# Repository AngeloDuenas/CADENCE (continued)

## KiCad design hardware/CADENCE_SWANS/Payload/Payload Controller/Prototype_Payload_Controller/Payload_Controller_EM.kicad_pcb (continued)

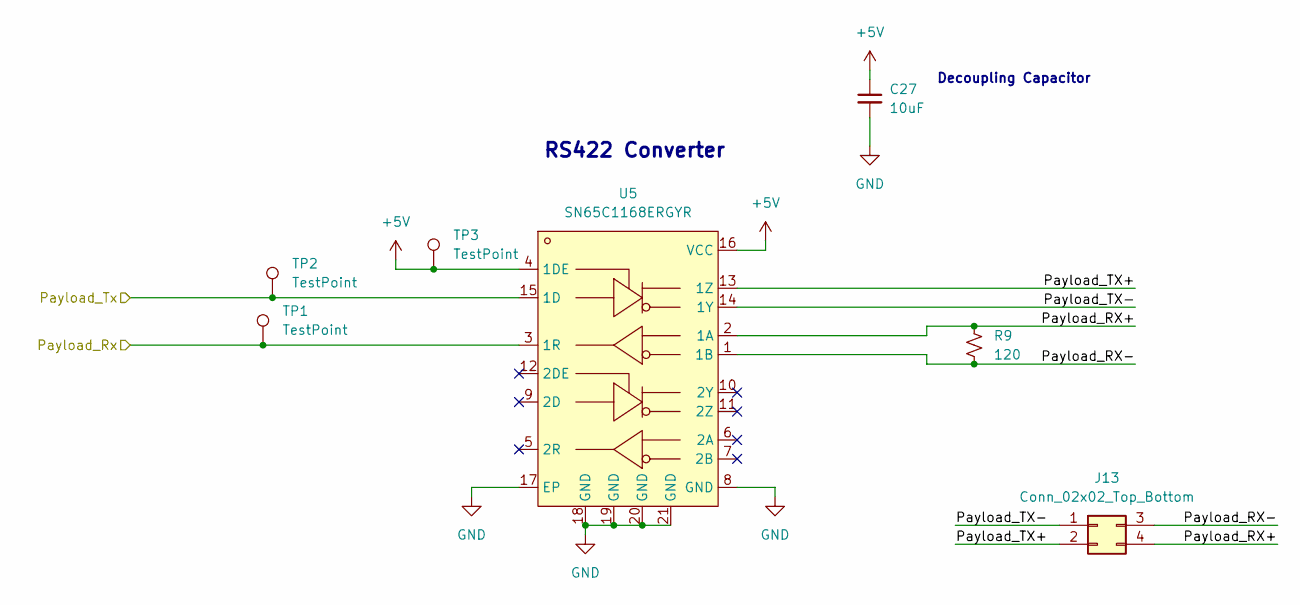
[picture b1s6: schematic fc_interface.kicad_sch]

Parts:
C27: 10uF; C_0603_1608Metric
J13: Conn_02x02_Top_Bottom; Hirose_DF11-4DP-2DSA_2x02_P2.00mm_Vertical
R9: 120; R_0603_1608Metric
TP1, TP2, TP3: TestPoint; TestPoint_Pad_1.0x1.0mm
U5: SN65C1168ERGYR; LCSC Part C201679

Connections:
+5V: C27.1, TP3.1, U5.4 (1DE), U5.16 (VCC); also elsewhere on the board
/Flight Computer Interface/Payload_RX+: J13.4, R9.1, U5.2 (1A)
/Flight Computer Interface/Payload_RX-: J13.3, R9.2, U5.1 (1B)
/Flight Computer Interface/Payload_TX+: J13.2, U5.13 (1Z)
/Flight Computer Interface/Payload_TX-: J13.1, U5.14 (1Y)
/Microcontroller/URXD2: TP1.1, U5.3 (1R); also elsewhere on the board
/Microcontroller/UTXD2: TP2.1, U5.15 (1D); also elsewhere on the board
GND: C27.2, U5.8 (GND), U5.17 (EP), U5.18 (GND), U5.19 (GND), U5.20 (GND), U5.21 (GND); also elsewhere on the board

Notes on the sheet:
RS422 Converter
Decoupling Capacitor

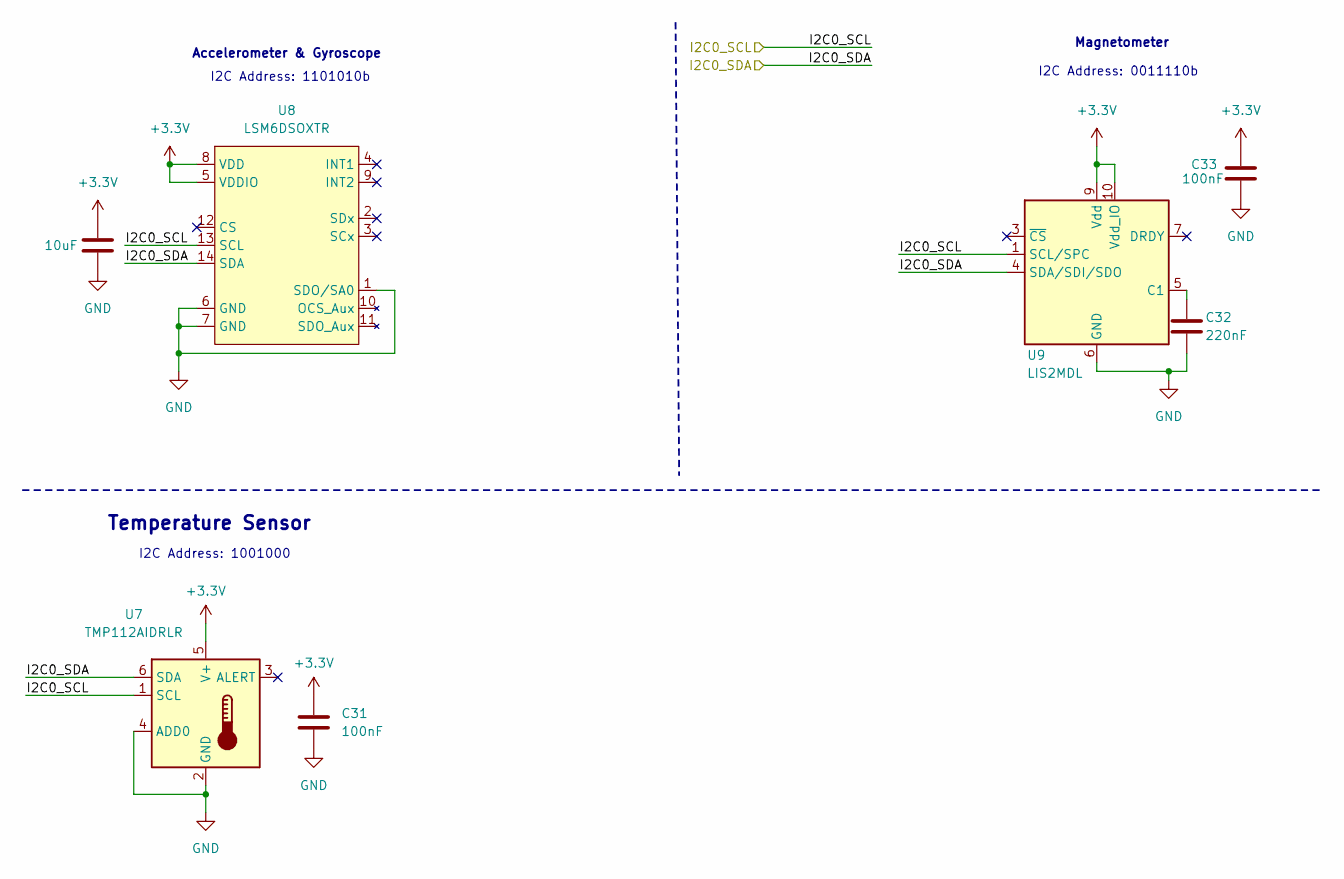
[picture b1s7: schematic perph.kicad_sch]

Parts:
C30: 10uF; C_0603_1608Metric
C31, C33: 100nF; C_0603_1608Metric
C32: 220nF; C_0603_1608Metric
U7: TMP112AIDRLR; SOT-563
U8: LSM6DSOXTR; LGA-14_L3.0-W2.5-P0.50-TL
U9: LIS2MDL; LGA-12_2x2mm_P0.5mm

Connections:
/Peripherals/I2C0_SCL: U7.1 (SCL), U8.13 (SCL), U9.1 (SCL/SPC); also elsewhere on the board
/Peripherals/I2C0_SDA: U7.6 (SDA), U8.14 (SDA), U9.4 (SDA/SDI/SDO); also elsewhere on the board
GND: C30.2, C31.2, C32.2, C33.2, U7.2 (GND), U7.4 (ADD0), U8.1 (SDO/SA0), U8.6 (GND), U8.7 (GND), U9.6 (GND), U9.8 (GND); also elsewhere on the board
unnamed: C32.1, U9.5 (C1)

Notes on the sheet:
Temperature Sensor
I2C Address: 0011110b
Accelerometer & Gyroscope
Magnetometer
I2C Address: 1001000
I2C Address: 1101010b

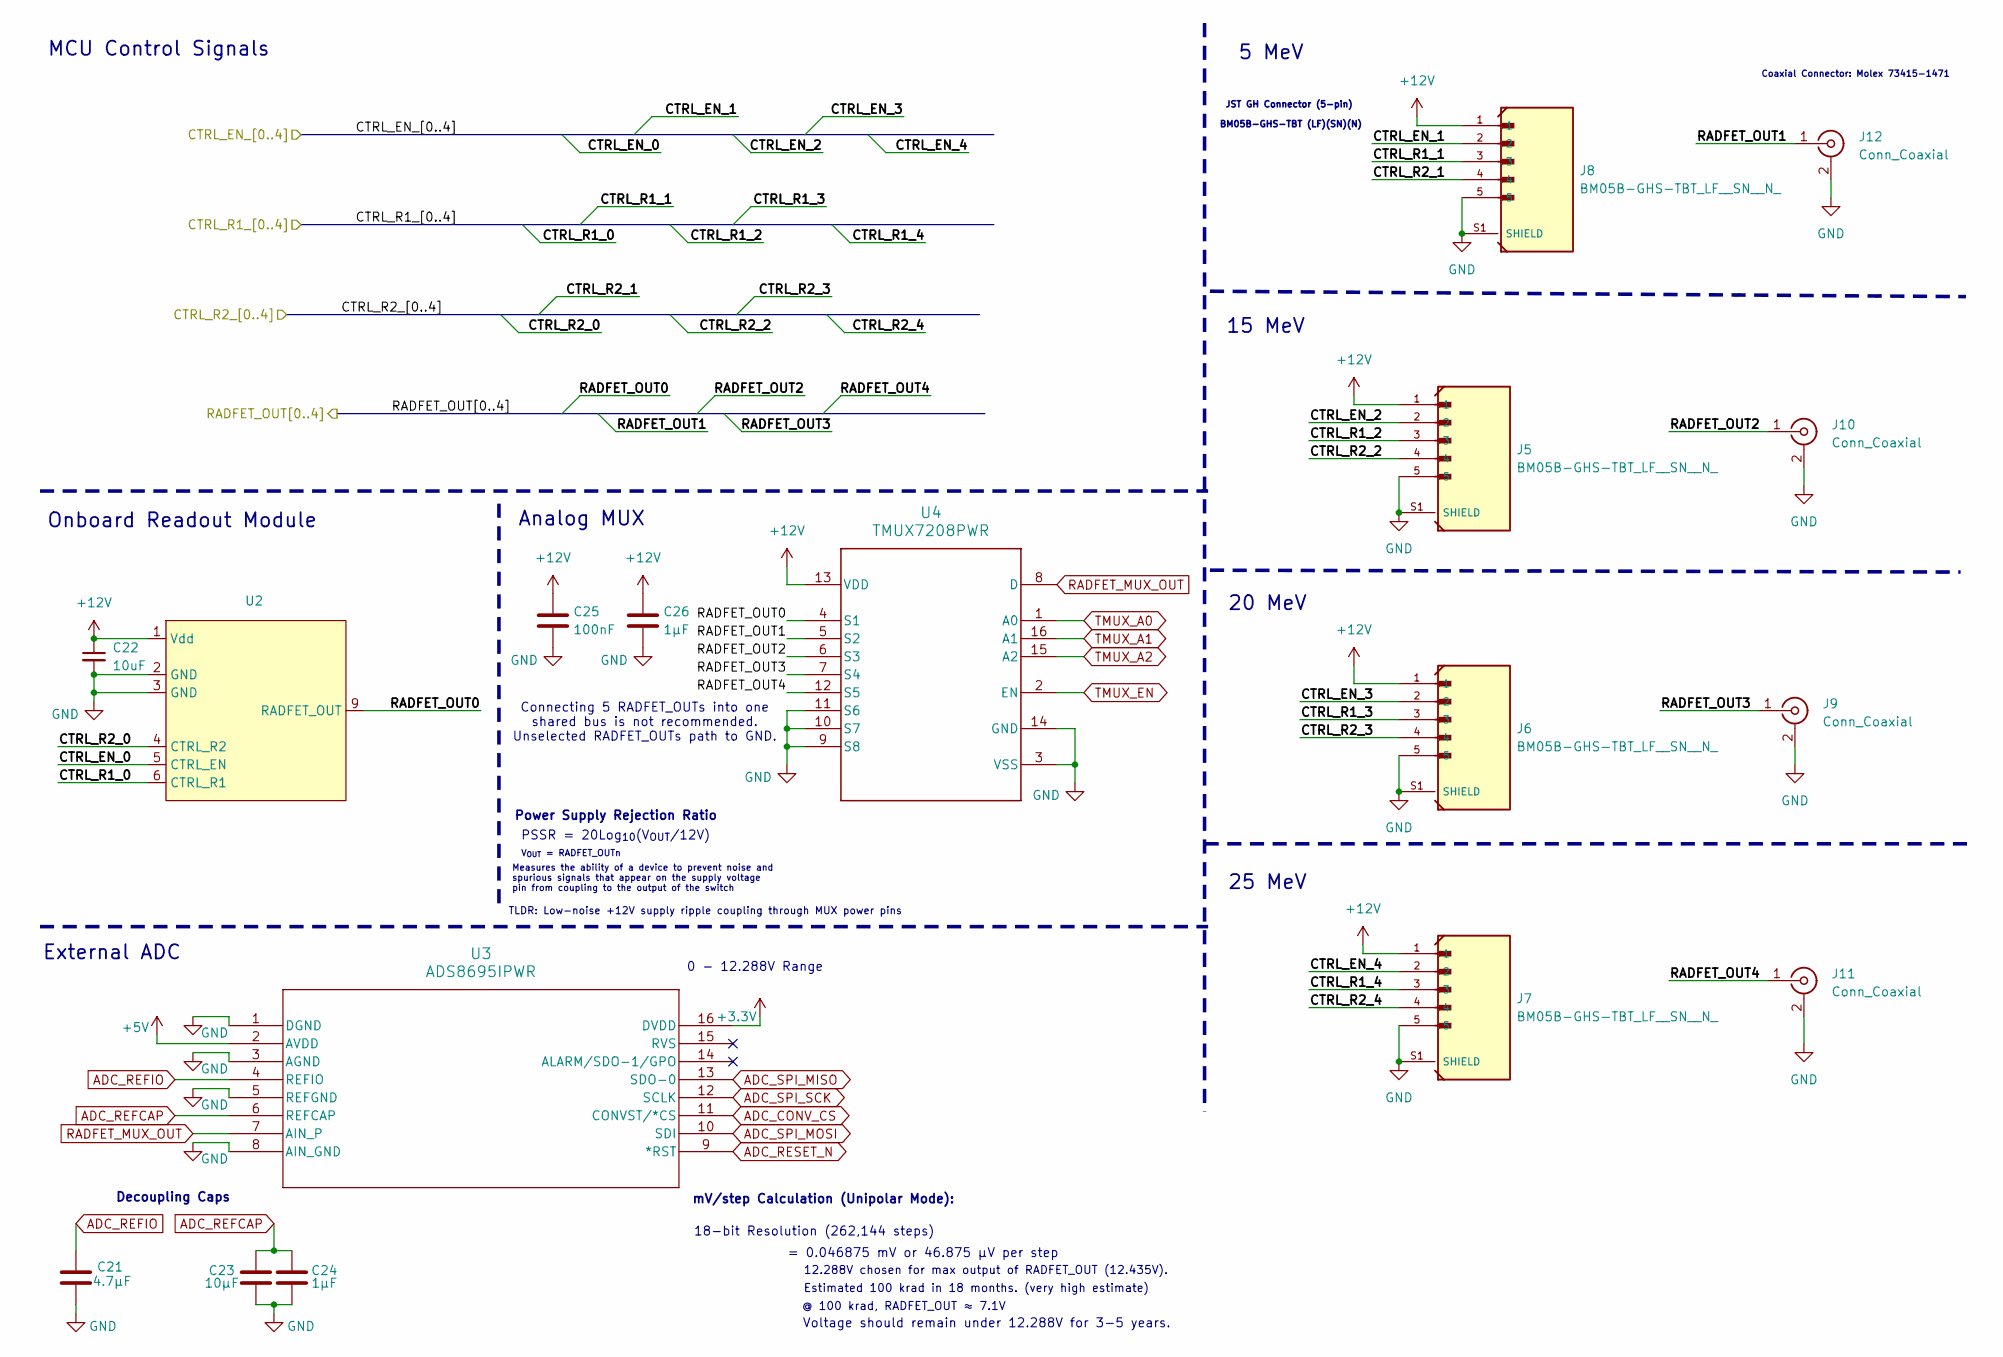
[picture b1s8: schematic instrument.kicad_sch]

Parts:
C21: 4.7µF; C_0805_2012Metric
C22: 10uF; C_1206_3216Metric
C23: 10µF; C_0805_2012Metric
C24, C26: 1µF; C_0603_1608Metric
C25: 100nF; C_0402_1005Metric
J5, J6, J7, J8: BM05B-GHS-TBT_LF__SN__N_; JST_BM05B-GHS-TBT_LF__SN__N_; MPN BM05B-GHS-TBT (LF)(SN)(N)
J9, J10, J11, J12: Conn_Coaxial; MMCX_Molex_73415-1471_Vertical
U2: RM-VT01-A
U3: ADS8695IPWR; PW16_TEX
U4: TMUX7208PWR; PW0016A_L

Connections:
+5V: U3.2 (AVDD); also elsewhere on the board
+12V: C22.1, C25.1, C26.1, J5.1, J6.1, J7.1, J8.1, U2.1 (Vdd), U4.13 (VDD); also elsewhere on the board
/Instrument/CTRL_EN_0: U2.5 (CTRL_EN); also elsewhere on the board
/Instrument/CTRL_EN_1: J8.2; also elsewhere on the board
/Instrument/CTRL_EN_2: J5.2; also elsewhere on the board
/Instrument/CTRL_EN_3: J6.2; also elsewhere on the board
/Instrument/CTRL_EN_4: J7.2; also elsewhere on the board
/Instrument/CTRL_R1_0: U2.6 (CTRL_R1); also elsewhere on the board
/Instrument/CTRL_R1_1: J8.3; also elsewhere on the board
/Instrument/CTRL_R1_2: J5.3; also elsewhere on the board
/Instrument/CTRL_R1_3: J6.3; also elsewhere on the board
/Instrument/CTRL_R1_4: J7.3; also elsewhere on the board
/Instrument/CTRL_R2_0: U2.4 (CTRL_R2); also elsewhere on the board
/Instrument/CTRL_R2_1: J8.4; also elsewhere on the board
/Instrument/CTRL_R2_2: J5.4; also elsewhere on the board
/Instrument/CTRL_R2_3: J6.4; also elsewhere on the board
/Instrument/CTRL_R2_4: J7.4; also elsewhere on the board
/Instrument/RADFET_OUT0: U2.9 (RADFET_OUT), U4.4 (S1)
/Instrument/RADFET_OUT1: J12.1 (In), U4.5 (S2)
/Instrument/RADFET_OUT2: J10.1 (In), U4.6 (S3)
/Instrument/RADFET_OUT3: J9.1 (In), U4.7 (S4)
/Instrument/RADFET_OUT4: J11.1 (In), U4.12 (S5)
ADC_CONV_CS: U3.11 (CONVST/*CS); also elsewhere on the board
ADC_REFCAP: C23.2, C24.2, U3.6 (REFCAP)
ADC_REFIO: C21.2, U3.4 (REFIO)
ADC_RESET_N: U3.9 (*RST); also elsewhere on the board
ADC_SPI_MISO: U3.13 (SDO-0); also elsewhere on the board
ADC_SPI_MOSI: U3.10 (SDI); also elsewhere on the board
ADC_SPI_SCK: U3.12 (SCLK); also elsewhere on the board
GND: C21.1, C22.2, C23.1, C24.1, C25.2, C26.2, J5.5, J5.S1 (SHIELD), J5.S2 (SHIELD), J6.5, J6.S1 (SHIELD), J6.S2 (SHIELD), J7.5, J7.S1 (SHIELD), J7.S2 (SHIELD), J8.5, J8.S1 (SHIELD), J8.S2 (SHIELD), J9.2 (Ext), J10.2 (Ext), J11.2 (Ext), J12.2 (Ext), U2.2 (GND), U2.3 (GND), U3.1 (DGND), U3.3 (AGND), U3.5 (REFGND), U3.8 (AIN_GND), U4.3 (VSS), U4.9 (S8), U4.10 (S7), U4.11 (S6), U4.14 (GND); also elsewhere on the board
RADFET_MUX_OUT: U3.7 (AIN_P), U4.8 (D)
TMUX_A0: U4.1 (A0); also elsewhere on the board
TMUX_A1: U4.16 (A1); also elsewhere on the board
TMUX_A2: U4.15 (A2); also elsewhere on the board
TMUX_EN: U4.2 (EN); also elsewhere on the board

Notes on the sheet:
Estimated 100 krad in 18 months. (very high estimate)
JST GH Connector (5-pin)
15 MeV
Voltage should remain under 12.288V for 3-5 years.
Onboard Readout Module
0 - 12.288V Range
Decoupling Caps
External ADC
5 MeV
18-bit Resolution (262,144 steps)
Analog MUX
@ 100 krad, RADFET_OUT ≈ 7.1V
TLDR: Low-noise +12V supply ripple coupling through MUX power pins
= 0.046875 mV or 46.875 µV per step
Coaxial Connector: Molex 73415-1471
Power Supply Rejection Ratio
MCU Control Signals
Measures the ability of a device to prevent noise and spurious signals that appear on the supply voltage pin from coupling to the output of the switch
PSSR = 20Log_{10}(V_{OUT}/12V)
BM05B-GHS-TBT (LF)(SN)(N)
Connecting 5 RADFET_OUTs into one shared bus is not recommended. Unselected RADFET_OUTs path to GND.
mV/step Calculation (Unipolar Mode):
12.288V chosen for max output of RADFET_OUT (12.435V).
20 MeV
V_{OUT} = RADFET_OUTn
25 MeV

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
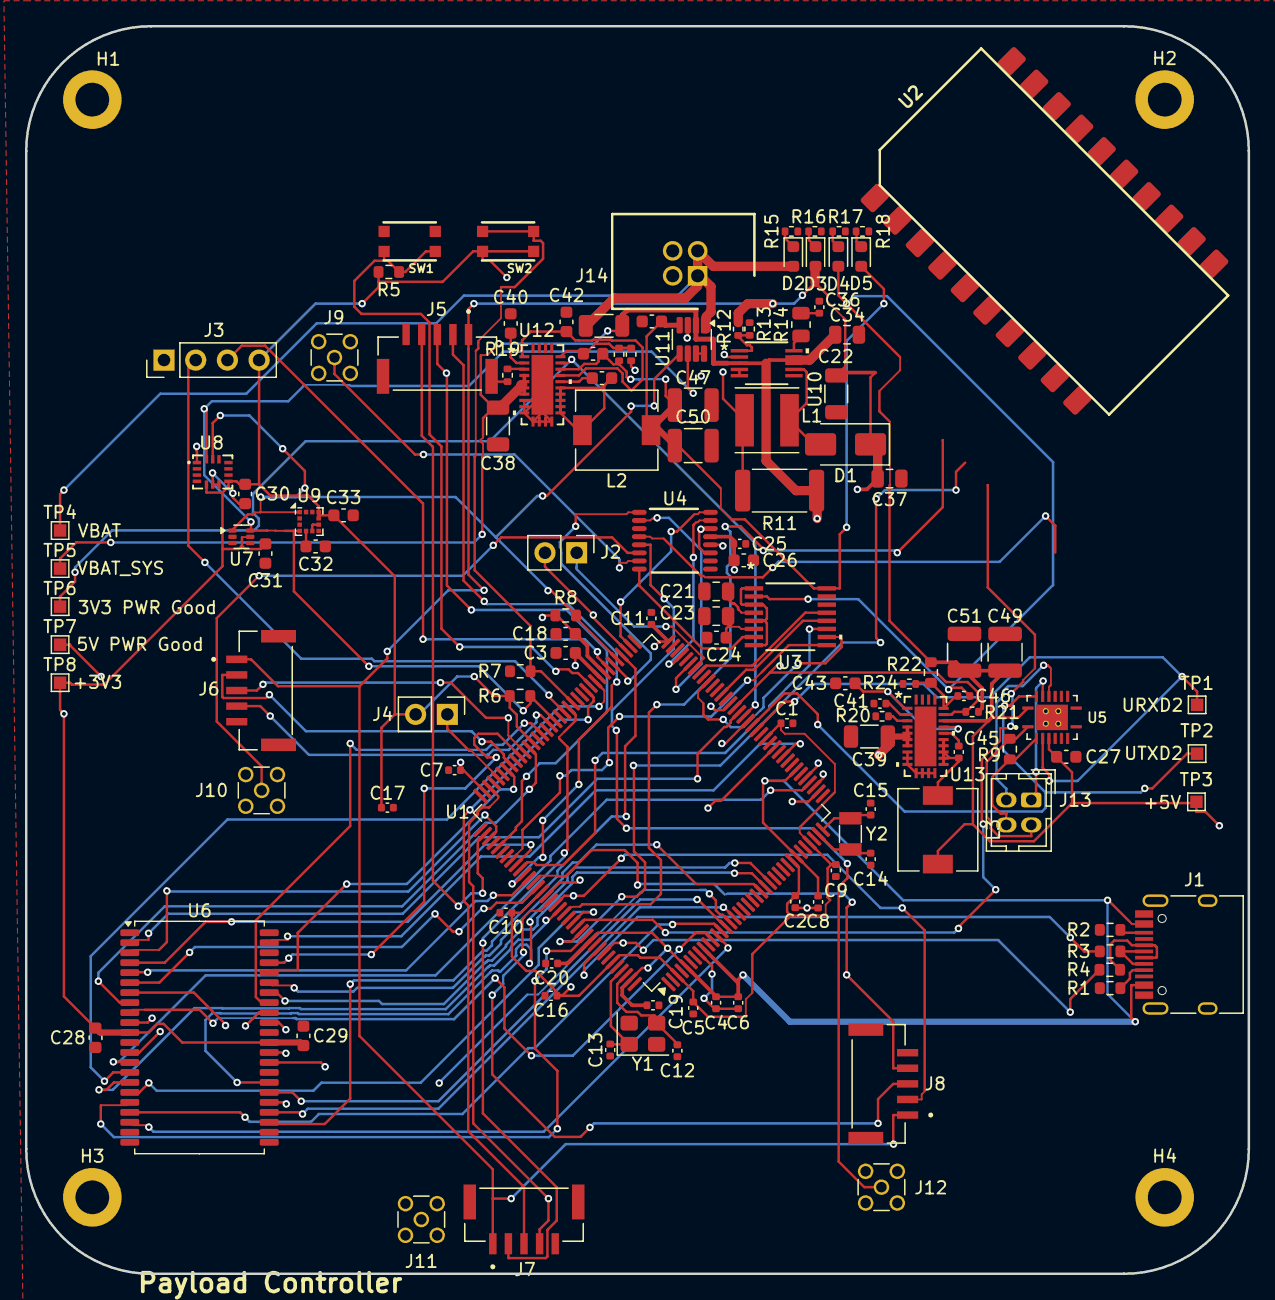
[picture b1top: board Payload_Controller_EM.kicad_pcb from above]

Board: 4 copper layers, 98.0 x 100.0 mm, 127 parts (0 on the bottom side), 120 nets.

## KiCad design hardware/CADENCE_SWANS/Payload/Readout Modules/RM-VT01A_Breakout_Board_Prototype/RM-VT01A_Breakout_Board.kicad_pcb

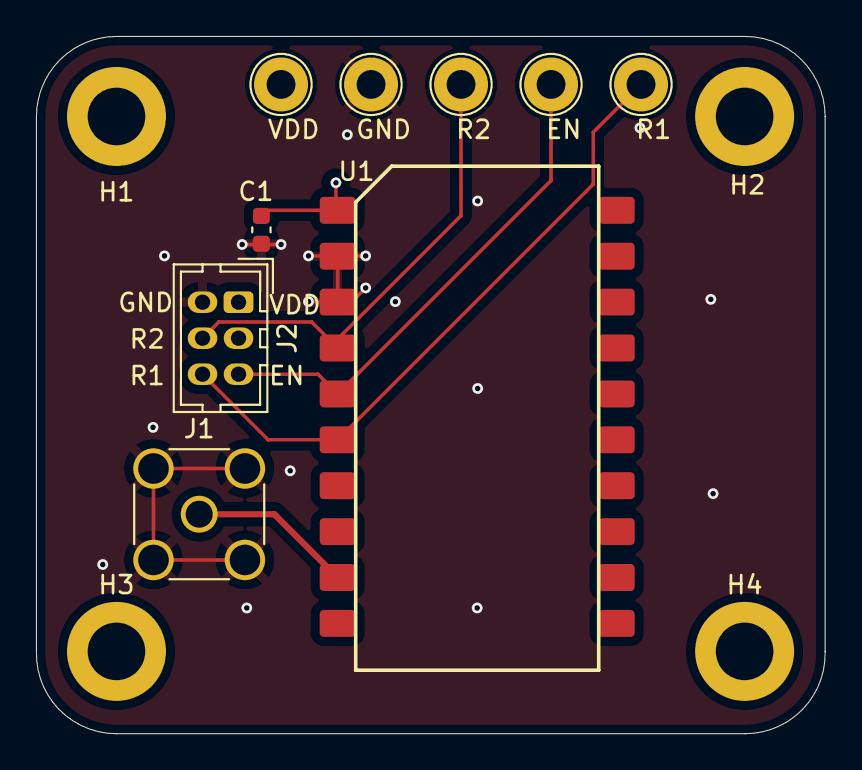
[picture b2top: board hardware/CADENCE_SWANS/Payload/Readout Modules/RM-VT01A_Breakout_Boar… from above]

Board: 4 copper layers, 43.8 x 38.7 mm, 13 parts (0 on the bottom side), 6 nets.

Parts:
C1: 10uF; C_0603_1608Metric
EN: TestPoint; TestPoint_Loop_D2.60mm_Drill1.6mm_Beaded
GND: TestPoint; TestPoint_Loop_D2.60mm_Drill1.6mm_Beaded
H1, H2, H3, H4: MountingHole; MountingHole_3.2mm_M3_ISO14580_Pad
J1: Conn_Coaxial; SMA_Amphenol_132291_Vertical
J2: Conn_01x06; PinHeader_2x03_P2.00mm_Vertical
R1, R2: TestPoint; TestPoint_Loop_D2.60mm_Drill1.6mm_Beaded
U1: RM-VT01-A
VDD: TestPoint; TestPoint_Loop_D2.60mm_Drill1.6mm_Beaded

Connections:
CTRL_EN: EN.1, J2.5, U1.5 (CTRL_EN)
CTRL_R1: J2.6, R1.1, U1.6 (CTRL_R1)
CTRL_R2: J2.4, R2.1, U1.4 (CTRL_R2)
GND: C1.2, GND.1, J1.2 (Ext), J2.2, U1.2 (GND), U1.3 (GND)
unnamed: J1.1 (In), U1.9 (RADFET_OUT)
VDD: C1.1, J2.1, U1.1 (Vdd), VDD.1

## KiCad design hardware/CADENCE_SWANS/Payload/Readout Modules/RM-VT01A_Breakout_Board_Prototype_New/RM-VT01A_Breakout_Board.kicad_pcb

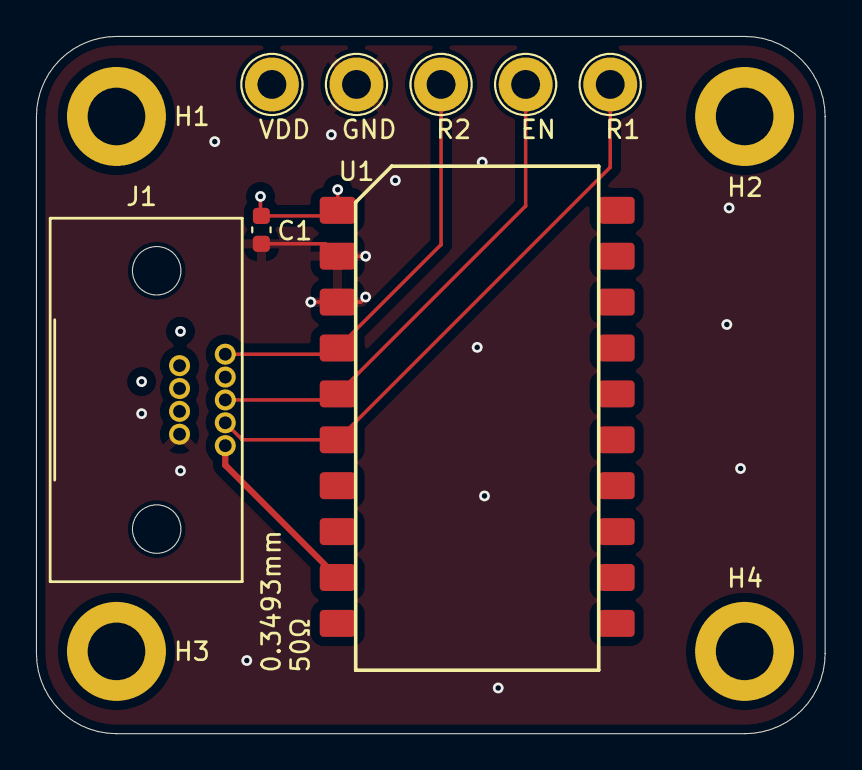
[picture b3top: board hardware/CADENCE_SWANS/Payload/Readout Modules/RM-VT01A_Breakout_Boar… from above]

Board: 4 copper layers, 43.8 x 38.7 mm, 12 parts (0 on the bottom side), 6 nets.

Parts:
C1: 10uF; C_0603_1608Metric
EN: TestPoint; TestPoint_Loop_D2.60mm_Drill1.6mm_Beaded
GND: TestPoint; TestPoint_Loop_D2.60mm_Drill1.6mm_Beaded
H1, H2, H3, H4: MountingHole; MountingHole_3.2mm_M3_ISO14580_Pad
J1: DE9_Pins; CONN_381-009_NRC
R1, R2: TestPoint; TestPoint_Loop_D2.60mm_Drill1.6mm_Beaded
U1: RM-VT01-A
VDD: TestPoint; TestPoint_Loop_D2.60mm_Drill1.6mm_Beaded

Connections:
CONN_COAXIAL: J1.5, U1.9 (RADFET_OUT)
CTRL_EN: EN.1, J1.3, U1.5 (CTRL_EN)
CTRL_R1: J1.4, R1.1, U1.6 (CTRL_R1)
CTRL_R2: J1.1, R2.1, U1.4 (CTRL_R2)
GND: C1.2, GND.1, J1.9, U1.2 (GND), U1.3 (GND)
VDD: C1.1, J1.6, U1.1 (Vdd), VDD.1

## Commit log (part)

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2026-05-01 Layout v2
    added courtyards, grouped components per datasheet specs. unsure of load switch placement. still figuring out ldo 150u cap.
